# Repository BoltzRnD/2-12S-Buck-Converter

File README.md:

# 2-12S-Buck-Converter
Open Source Hardware Board for LM5148 Based Power Brick

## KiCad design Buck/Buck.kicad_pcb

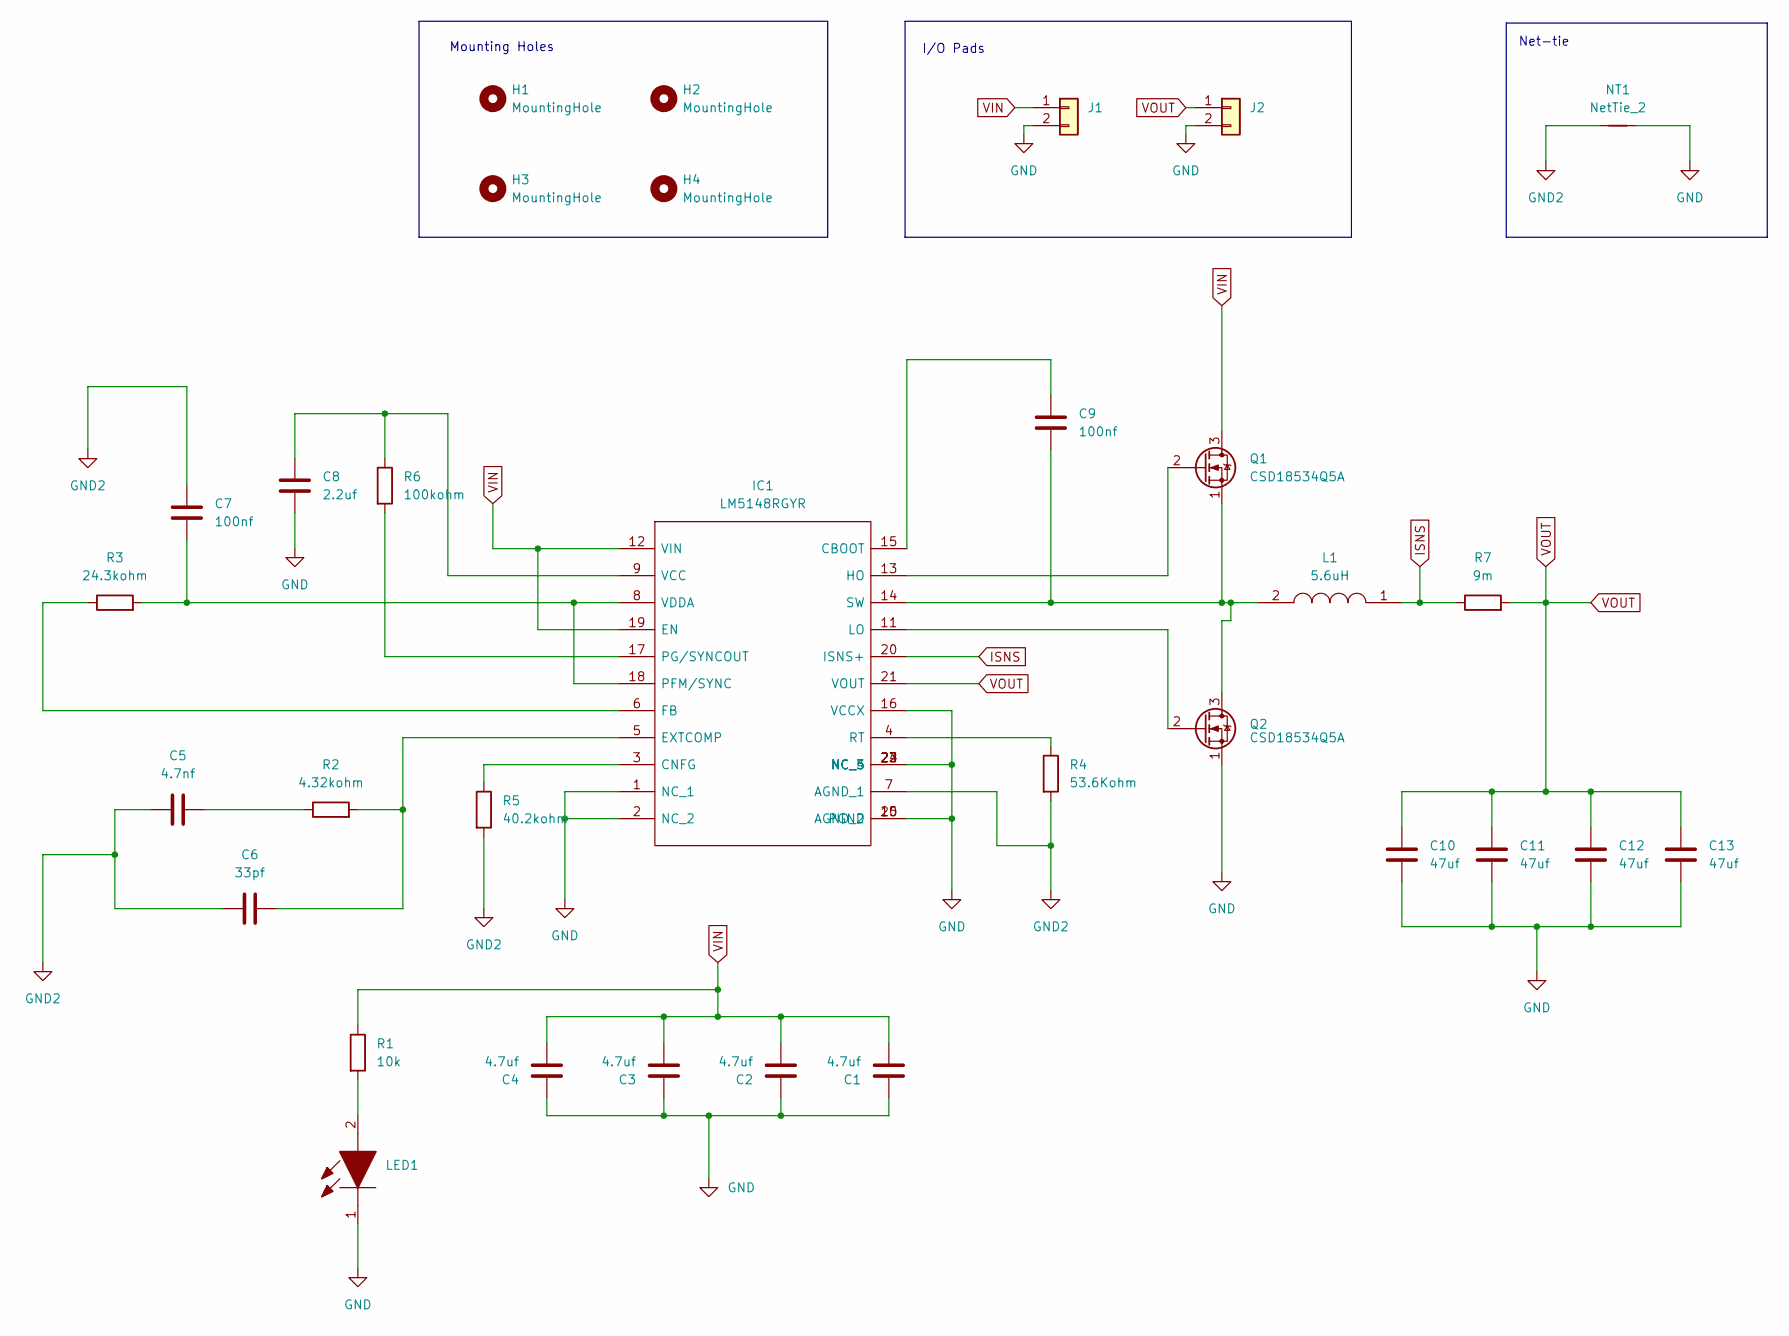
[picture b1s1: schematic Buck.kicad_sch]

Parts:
C1, C3, C4: 4.7uf; C_1210_3225Metric; LCSC NO C381466
C2: 4.7uf; C_1210_3225Metric
C5: 4.7nf; C_0805_2012Metric; LCSC NO C2176990
C6: 33pf; C_0805_2012Metric; LCSC NO C1814
C7, C9: 100nf; C_0402_1005Metric; LCSC NO C71687
C8: 2.2uf; C_0603_1608Metric; LCSC NO C86018
C10, C11, C12, C13: 47uf; C_1210_3225Metric; LCSC NO C77101
H1, H2, H3, H4: MountingHole; MountingHole_2.1mm
IC1: LM5148RGYR; Manufacturer_Part_Number LM5148RGYR; Mouser Part Number 595-LM5148RGYR
J1, J2: Conn_01x02; Untitled
L1: 5.6uH; HC35R6R; Manufacturer_Part_Number HC3-5R6-R; DIGIKEY NO 513-1756-ND
LED1: LEDM3216X120N; Manufacturer_Part_Number LTST-C150KRKT; LCSC NO C125086
NT1: NetTie_2; NetTie-2_SMD_Pad0.5mm
Q1, Q2: CSD18534Q5A; NEW; LCSC NO C115943
R1: 10k; C_0805_2012Metric; LCSC NO C723404
R2: 4.32kohm; C_0402_1005Metric; LCSC NO C2091540
R3: 24.3kohm; C_0402_1005Metric; LCSC NO C4137452
R4: 53.6Kohm; C_0603_1608Metric; LCSC NO C844576
R5: 40.2kohm; C_0603_1608Metric; LCSC NO C844784
R6: 100kohm; C_0603_1608Metric; LCSC NO C844916
R7: 9m; C_1206_3216Metric; Digikey no 541-10099-2-ND

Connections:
GND: C1.1, C2.1, C3.1, C4.1, C8.2, C10.2, C11.2, C12.2, C13.2, IC1.1 (NC_1), IC1.2 (NC_2), IC1.10 (PGND), IC1.16 (VCCX), IC1.22 (NC_3), IC1.23 (NC_4), IC1.24 (NC_5), IC1.25 (AGND_2), J1.2, J2.2, LED1.1, NT1.2, Q2.1 (S)
GND2: C5.2, C6.2, C7.1, IC1.7 (AGND_1), NT1.1, R4.2, R5.2
ISNS: IC1.20 (ISNS+), L1.1, R7.1
unnamed: C5.1, R2.1
unnamed: C9.2, IC1.15 (CBOOT)
unnamed: IC1.3 (CNFG), R5.1
unnamed: C6.1, IC1.5 (EXTCOMP), R2.2
unnamed: IC1.6 (FB), R3.1
unnamed: IC1.13 (HO), Q1.2 (G)
unnamed: IC1.11 (LO), Q2.2 (G)
unnamed: C7.2, IC1.8 (VDDA), IC1.18 (PFM/SYNC), R3.2
unnamed: IC1.17 (PG/SYNCOUT), R6.2
unnamed: IC1.4 (RT), R4.1
unnamed: C9.1, IC1.14 (SW), L1.2, Q1.1 (S), Q2.3 (D)
unnamed: C8.1, IC1.9 (VCC), R6.1
unnamed: LED1.2, R1.2
VIN: C1.2, C2.2, C3.2, C4.2, IC1.12 (VIN), IC1.19 (EN), J1.1, Q1.3 (D), R1.1
VOUT: C10.1, C11.1, C12.1, C13.1, IC1.21 (VOUT), J2.1, R7.2

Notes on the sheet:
I/O Pads
Net-tie
Mounting Holes

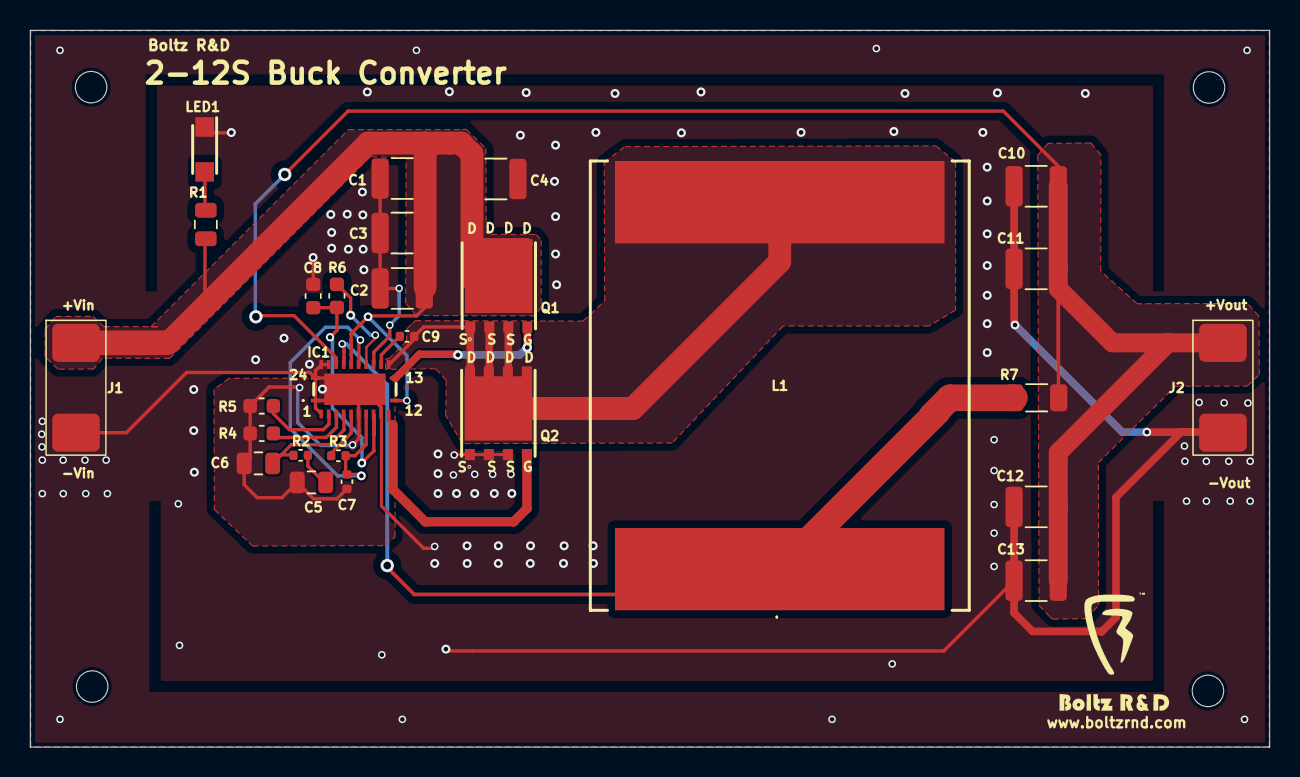
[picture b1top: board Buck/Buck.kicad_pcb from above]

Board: 2 copper layers, 82.8 x 47.9 mm, 32 parts (0 on the bottom side), 18 nets.

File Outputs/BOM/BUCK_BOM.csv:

"Reference","Qty","Value","DNP","Exclude from BOM","Exclude from Board","Footprint","Datasheet"
"R7","1","9m","","","","Capacitor_SMD:C_1206_3216Metric","~"
"R6","1","100kohm","","","","Capacitor_SMD:C_0603_1608Metric","~"
"R5","1","40.2kohm","","","","Capacitor_SMD:C_0603_1608Metric","~"
"R4","1","53.6Kohm","","","","Capacitor_SMD:C_0603_1608Metric","~"
"R3","1","24.3kohm","","","","Capacitor_SMD:C_0402_1005Metric","~"
"R2","1","4.32kohm","","","","Capacitor_SMD:C_0402_1005Metric","~"
"R1","1","10k","","","","Capacitor_SMD:C_0805_2012Metric","~"
"Q1,Q2","2","CSD18534Q5A","","","","CSD18534Q5A_:NEW","https://www.lcsc.com/datasheet/lcsc_datasheet_2410010301_Tex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"
"NT1","1","NetTie_2","","","","NetTie:NetTie-2_SMD_Pad0.5mm","~"
"LED1","1","~","","","","LTST-C150KRKT:LEDM3216X120N","https://optoelectronics.liteon.com/upload/download/DS-22-99-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"
"L1","1","5.6uH","","","","HC3-5R6-R:HC35R6R","https://datasheet.datasheetarchive.com/originals/distributor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"
"J1,J2","2","Conn_01x02","","","","pad_footprint:Untitled","~"
"IC1","1","LM5148RGYR","","","","LM5148_:LM5148RGYR","https://www.ti.com/lit/ds/symlink/lm5148.pdf?ts=168099021057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"
"H1,H2,H3,H4","4","MountingHole","","","","MountingHole:MountingHole_2.1mm","~"
"C10,C11,C12,C13","4","47uf","","","","Capacitor_SMD:C_1210_3225Metric","~"
"C8","1","2.2uf","","","","Capacitor_SMD:C_0603_1608Metric","~"
"C7,C9","2","100nf","","","","Capacitor_SMD:C_0402_1005Metric","~"
"C6","1","33pf","","","","Capacitor_SMD:C_0805_2012Metric","~"
"C5","1","4.7nf","","","","Capacitor_SMD:C_0805_2012Metric","~"
"C1,C2,C3,C4","4","4.7uf","","","","Capacitor_SMD:C_1210_3225Metric","~"

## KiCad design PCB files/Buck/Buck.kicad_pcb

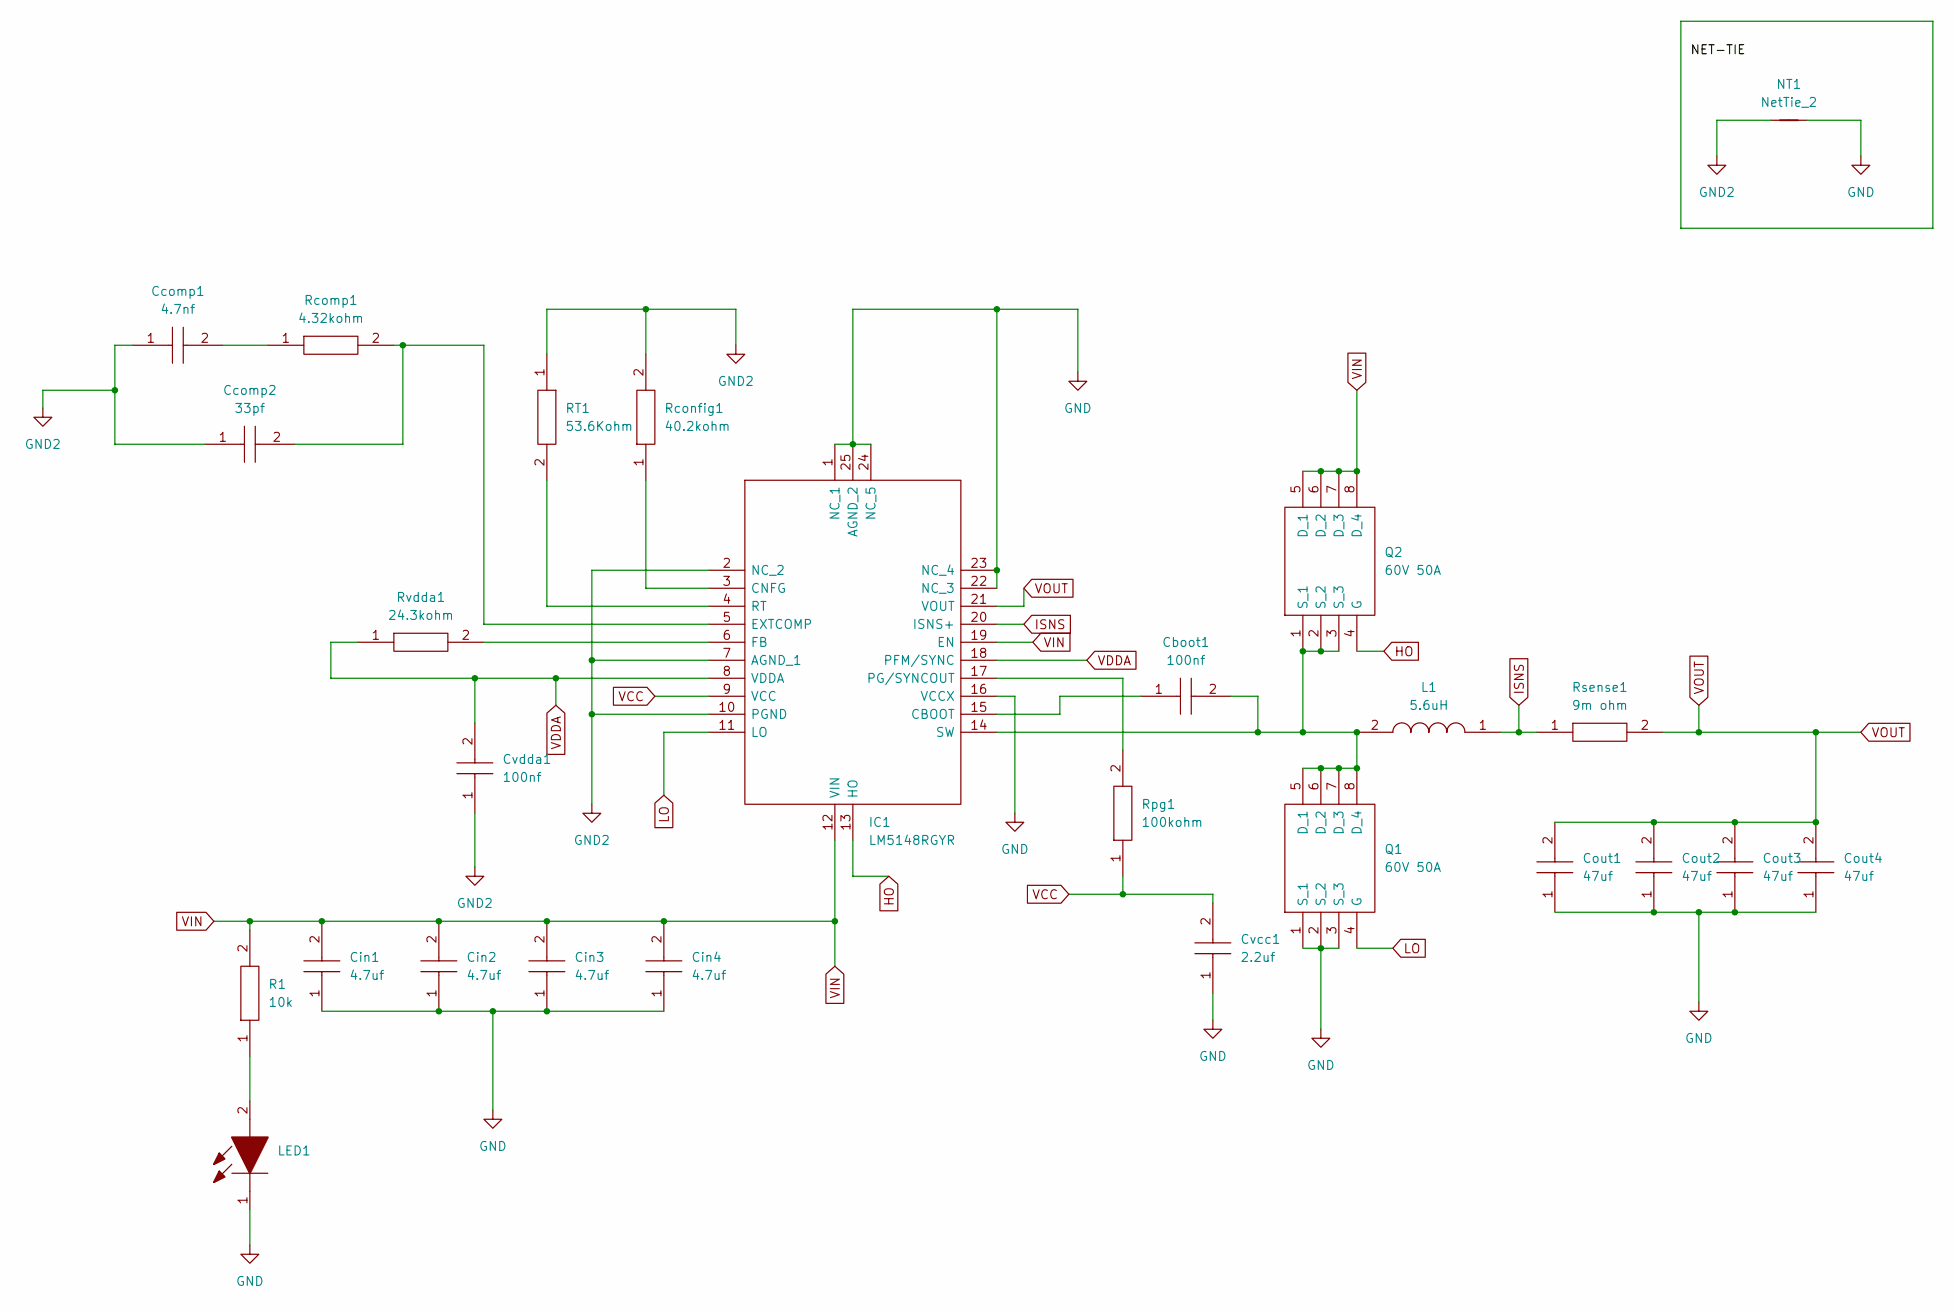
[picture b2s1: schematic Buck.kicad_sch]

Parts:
Cboot1: 100nf; CAPC1005X70N; Manufacturer_Part_Number GRM155R71A104KA01D; LCSC NO C71687
Ccomp1: 4.7nf; CAPC2012X75N; Manufacturer_Part_Number CGA4C2C0G1H472J060AA; LCSC no C2176990
Ccomp2: 33pf; CAPC2012X75N; Manufacturer_Part_Number CL21C330JBANNNC; LCSC NO C1814
Cin1, Cin2, Cin3, Cin4: 4.7uf; CAPC3225X200N; Manufacturer_Part_Number FS32X475K101EGG; LCSC NO C381466
Cout1, Cout2, Cout3, Cout4: 47uf; CAPC3225X270N; Manufacturer_Part_Number GRM32ER61C476KE15L; LCSC NO C77101
Cvcc1: 2.2uf; CAPC3225X270N; Manufacturer_Part_Number GRM188R71A225KE15D; LCSC NO C86018
Cvdda1: 100nf; CAPC1005X70N; Manufacturer_Part_Number GRM155R71A104KA01D; LCSC NO C71687
IC1: LM5148RGYR; Manufacturer_Part_Number LM5148RGYR; Mouser Part Number 595-LM5148RGYR
L1: 5.6uH; HC35R6R; Manufacturer_Part_Number HC3-5R6-R; DIGIKEY NO 513-1756-ND
LED1: LEDM3216X120N; Manufacturer_Part_Number LTST-C150KRKT; LCSC NO C125086
NT1: NetTie_2; NetTie-2_SMD_Pad0.5mm
Q1, Q2: 60V 50A; Q5A; Manufacturer_Part_Number CSD18534Q5A; Mouser Part Number 595-CSD18534Q5A
R1: 10k; RESC2013X84N; Manufacturer_Part_Number RC0805FR-7W10KL; lcsc no C723404
RT1: 53.6Kohm; RESC1005X40N; Manufacturer_Part_Number CRCW060353K6FKEA; LCSC NO C844576
Rcomp1: 4.32kohm; RESC1005X40N; Manufacturer_Part_Number CRCW04024K32FKED; LCSC no. C2091540
Rconfig1: 40.2kohm; RESC1608X50N; Manufacturer_Part_Number CRCW060340K2FKEA; LCSC NO C844784
Rpg1: 100kohm; RESC1005X40N; Manufacturer_Part_Number CRCW0603100KFKEA; LCSC NO C844916
Rsense1: 9m ohm; RESC3216X89N; Manufacturer_Part_Number WSLP12069L000FEA; Mouser Part Number 71-WSLP12069L000FEA
Rvdda1: 24.3kohm; RESC1005X40N; Manufacturer_Part_Number CRCW040224K3FKED; LCSC NO C4137452

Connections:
GND: Cin1.1, Cin2.1, Cin3.1, Cin4.1, Cout1.1, Cout2.1, Cout3.1, Cout4.1, Cvcc1.1, IC1.1 (NC_1), IC1.16 (VCCX), IC1.22 (NC_3), IC1.23 (NC_4), IC1.24 (NC_5), IC1.25 (AGND_2), LED1.1, NT1.2, Q1.1 (S_1), Q1.2 (S_2), Q1.3 (S_3)
GND2: Ccomp1.1, Ccomp2.1, Cvdda1.1, IC1.2 (NC_2), IC1.7 (AGND_1), IC1.10 (PGND), NT1.1, RT1.1, Rconfig1.2
HO: IC1.13 (HO), Q2.4 (G)
ISNS: IC1.20 (ISNS+), L1.1, Rsense1.1
LO: IC1.11 (LO), Q1.4 (G)
unnamed: Ccomp1.2, Rcomp1.1
unnamed: Cboot1.1, IC1.15 (CBOOT)
unnamed: IC1.3 (CNFG), Rconfig1.1
unnamed: Ccomp2.2, IC1.5 (EXTCOMP), Rcomp1.2
unnamed: IC1.6 (FB), Rvdda1.2
unnamed: IC1.17 (PG/SYNCOUT), Rpg1.2
unnamed: IC1.4 (RT), RT1.2
unnamed: Cboot1.2, IC1.14 (SW), L1.2, Q1.5 (D_1), Q1.6 (D_2), Q1.7 (D_3), Q1.8 (D_4), Q2.1 (S_1), Q2.2 (S_2), Q2.3 (S_3)
unnamed: LED1.2, R1.1
VCC: Cvcc1.2, IC1.9 (VCC), Rpg1.1
VDDA: Cvdda1.2, IC1.8 (VDDA), IC1.18 (PFM/SYNC), Rvdda1.1
VIN: Cin1.2, Cin2.2, Cin3.2, Cin4.2, IC1.12 (VIN), IC1.19 (EN), Q2.5 (D_1), Q2.6 (D_2), Q2.7 (D_3), Q2.8 (D_4), R1.2
VOUT: Cout1.2, Cout2.2, Cout3.2, Cout4.2, IC1.21 (VOUT), Rsense1.2

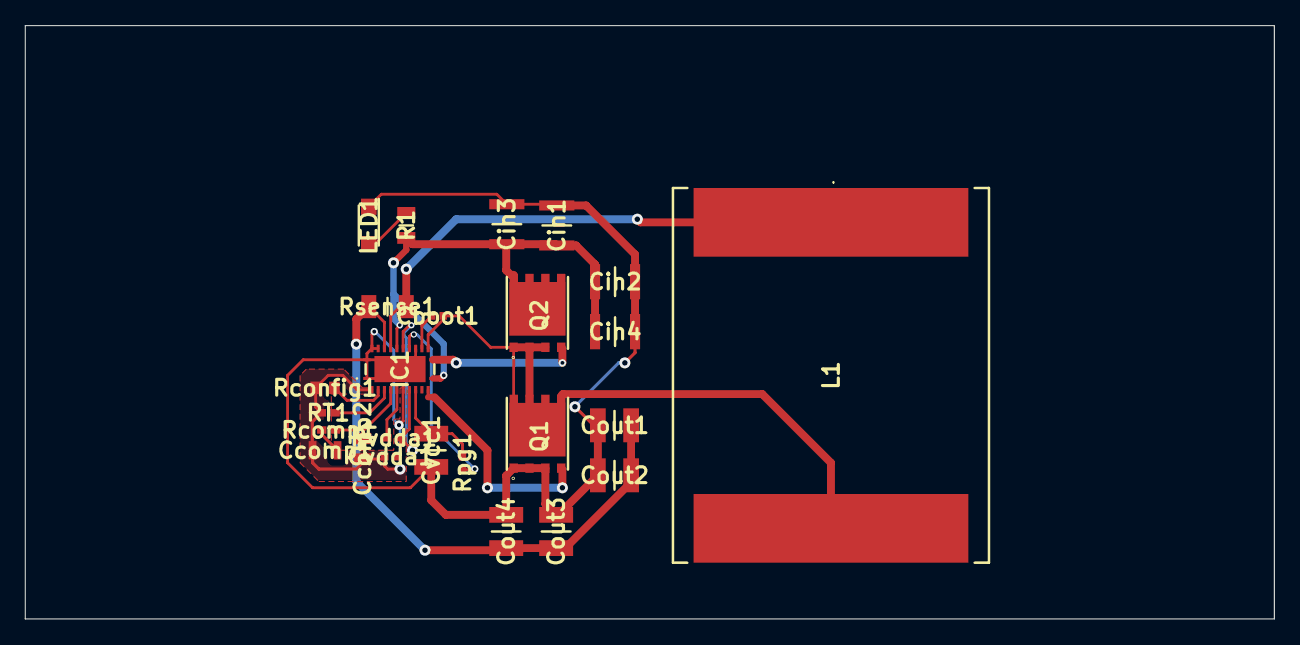
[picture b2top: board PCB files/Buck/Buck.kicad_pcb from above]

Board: 2 copper layers, 100.0 x 47.5 mm, 26 parts (1 on the bottom side), 18 nets.

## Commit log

2025-03-17 Create Libraries
2025-03-24 .updated
2025-03-25 UPDATED
    UPDATED
2025-03-25 silkscreen updated
2025-03-27 updates
    Connected all the unconnected nets, added polygon for vin, updated the polygons
2025-03-28 final updates
    straight polygons, straight tracks, Proper ERC, corrected the unrouted tracks
2025-03-29 updates
    solve all the drc issues
2025-03-31 logo added
    added the logo
2025-03-31 updated
    generated gerber file and added media files
